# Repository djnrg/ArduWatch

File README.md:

# ArduWatch
Watch Arduino AtHeart

In this project using Arduino Software and following hardweare:
     - ATMega328
     - OLED 1,3" display
     - RTC DS1307
     - Battery 3,7V

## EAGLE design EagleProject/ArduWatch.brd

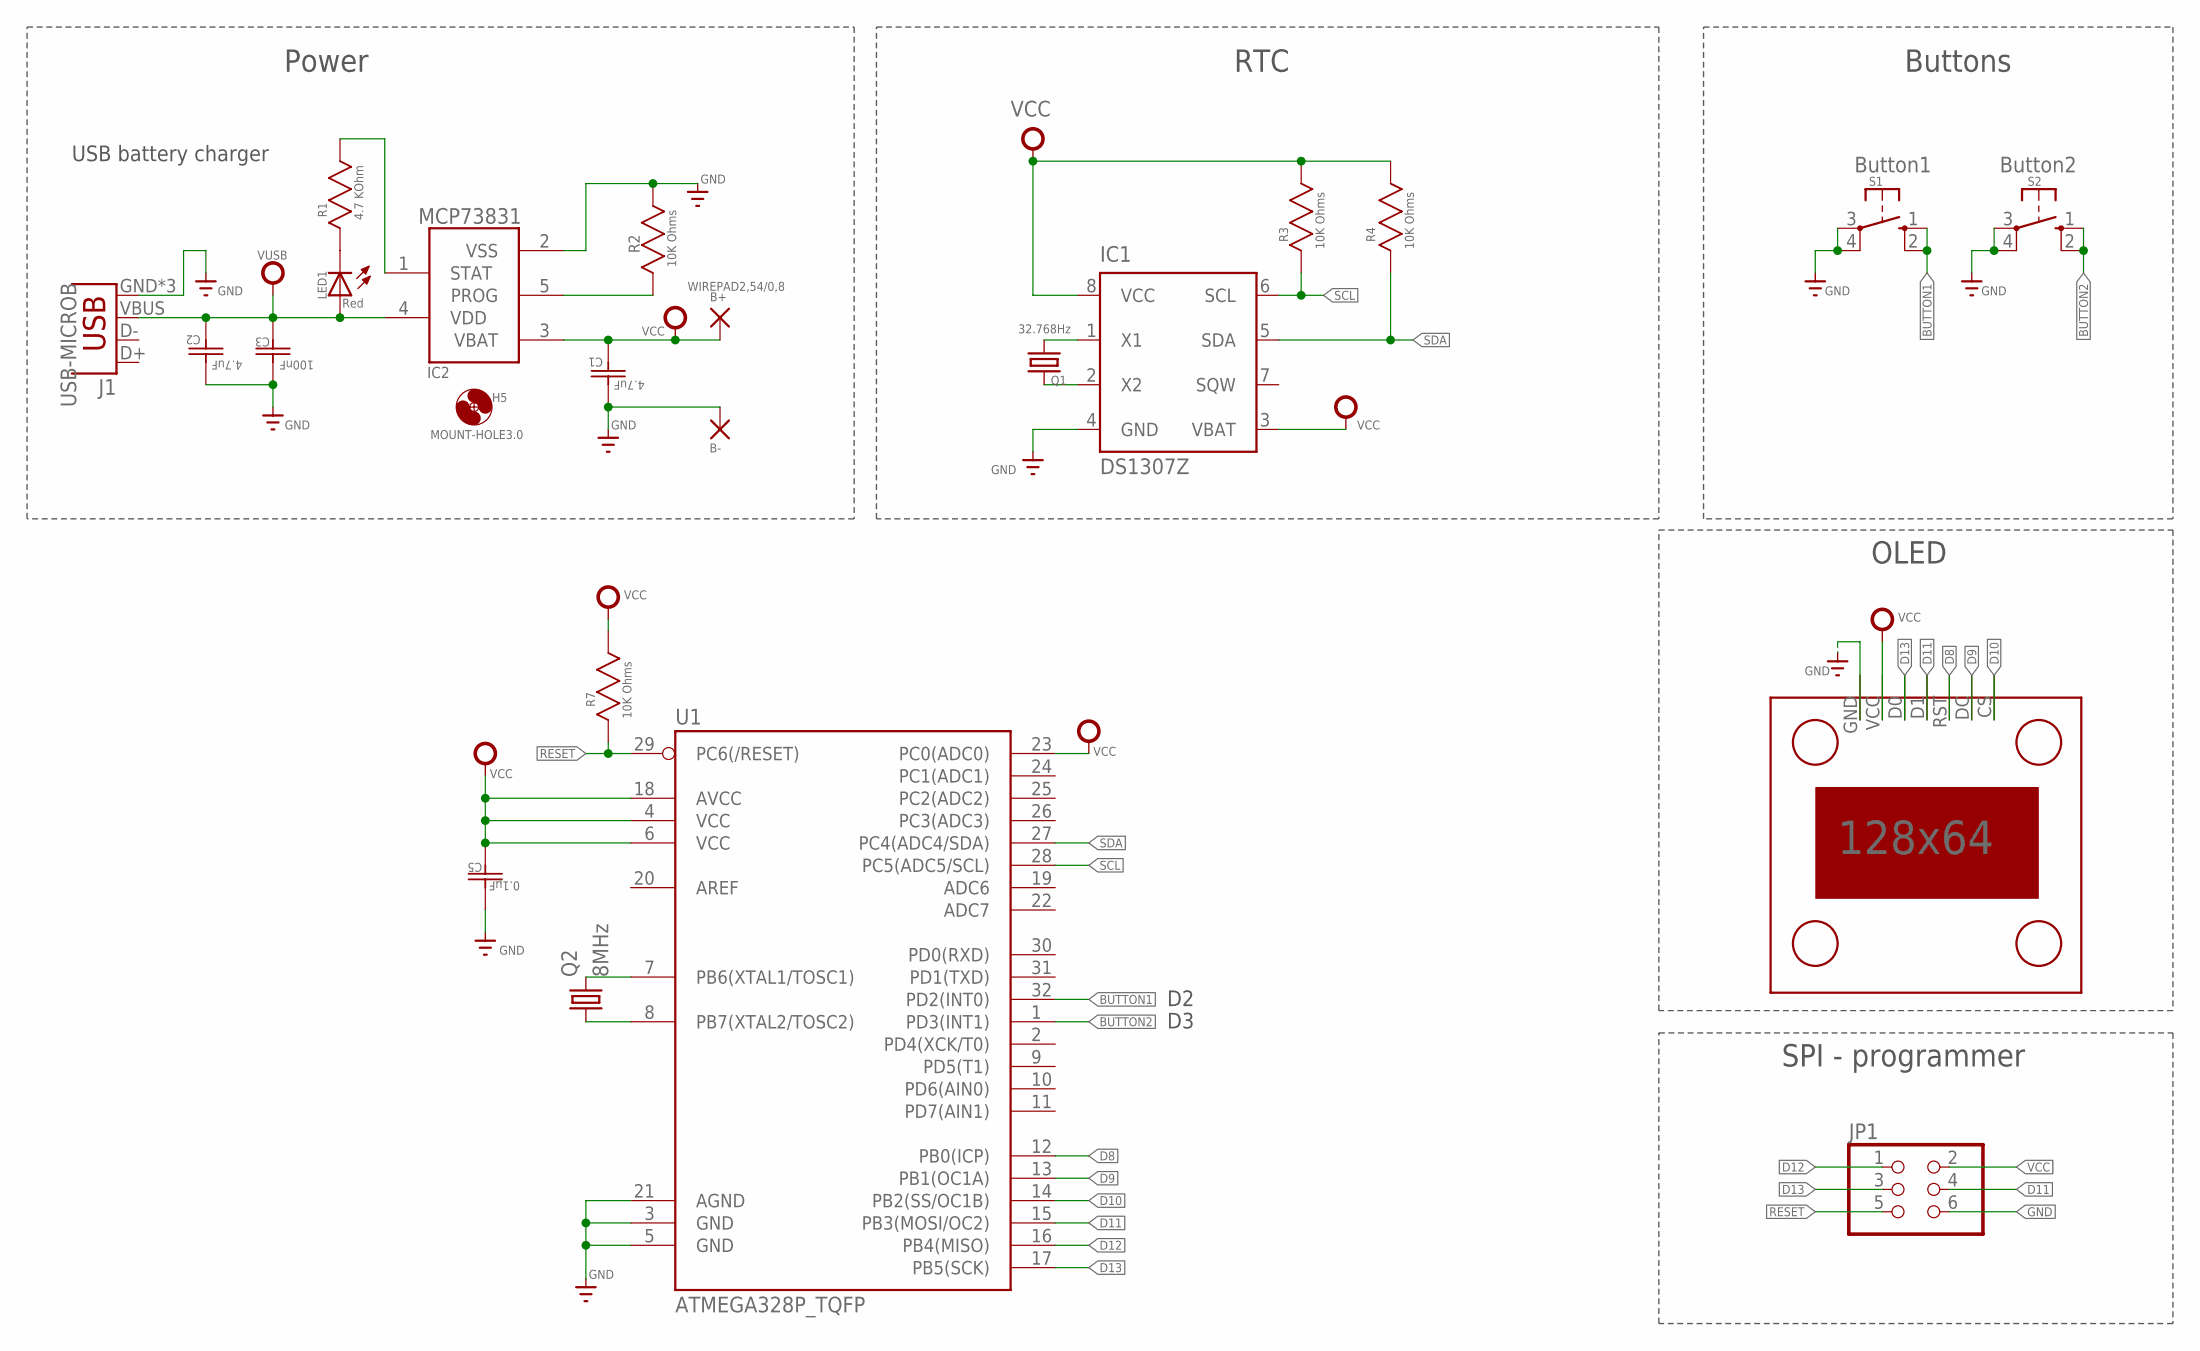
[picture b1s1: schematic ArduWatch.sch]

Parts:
1,3"OLED1: OLED; 1,3"OLED
B+: WIREPAD2,54/0,8; 2,54/0,8
B-: WIREPAD2,54/0,8; 2,54/0,8
C1, C2: 4.7uF; CAPC3216X180N
C3: 100nF; CAPC3216X88N
C5: 0.1µF; CAPC3216X94N
H5: MOUNT-HOLE3.0; 3,0
IC1: DS1307Z; SOIC8
IC2: MCP73831; SOT23-5L
J1: USB-MICROB
JP1: PINHD-2X3; 2X03
LED1: Red; CHIPLED_1206
Q1: 32.768Hz; TC26H
Q2: 8MHz; HC49/S
R1: 4.7 KOhm; RESC3216X71N
R2, R3, R4, R7: 10K Ohms; RESC3216X71N
S1: Button1; B3F-10XX
S2: Button2; B3F-10XX
U1: ATMEGA328P_TQFP; TQFP32-08

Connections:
BUTTON1: S1.1 (S), S1.2 (S1), U1.32 (PD2(INT0))
BUTTON2: S2.1 (S), S2.2 (S1), U1.1 (PD3(INT1))
D8: 1,3"OLED1.RST, U1.12 (PB0(ICP))
D9: 1,3"OLED1.DC, U1.13 (PB1(OC1A))
D10: 1,3"OLED1.CS, U1.14 (PB2(SS/OC1B))
D11: 1,3"OLED1.D1, JP1.4, U1.15 (PB3(MOSI/OC2))
D12: JP1.1, U1.16 (PB4(MISO))
D13: 1,3"OLED1.D0, JP1.3, U1.17 (PB5(SCK))
GND: 1,3"OLED1.GND, B-.1, C1.1 (C1), C2.1 (C1), C3.1 (C1), C5.1 (C1), IC1.4 (GND), IC2.2 (VSS), J1.GND, J1.MT1 (GND), J1.MT2 (GND), JP1.6, R2.1 (R1), S1.3, S1.4 (P1), S2.3, S2.4 (P1), U1.3 (GND), U1.5 (GND), U1.21 (AGND)
unnamed: LED1.C, R1.2 (R2)
unnamed: IC1.1 (X1), Q1.2
unnamed: IC2.1 (STAT), R1.1 (R1)
unnamed: IC2.5 (PROG), R2.2 (R2)
unnamed: IC1.2 (X2), Q1.1
unnamed: Q2.2, U1.7 (PB6(XTAL1/TOSC1))
unnamed: Q2.1, U1.8 (PB7(XTAL2/TOSC2))
RESET: JP1.5, R7.2 (R2), U1.29 (PC6(/RESET))
SCL: IC1.6 (SCL), R3.2 (R2), U1.28 (PC5(ADC5/SCL))
SDA: IC1.5 (SDA), R4.2 (R2), U1.27 (PC4(ADC4/SDA))
VCC: 1,3"OLED1.VCC, B+.1, C1.2 (C2), C5.2 (C2), IC1.3 (VBAT), IC1.8 (VCC), IC2.3 (VBAT), JP1.2, R3.1 (R1), R4.1 (R1), R7.1 (R1), U1.4 (VCC), U1.6 (VCC), U1.18 (AVCC), U1.23 (PC0(ADC0))
VUSB: C2.2 (C2), C3.2 (C2), IC2.4 (VDD), J1.VBUS, LED1.A

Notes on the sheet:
USB battery charger
Power
RTC
Buttons
OLED
SPI - programmer

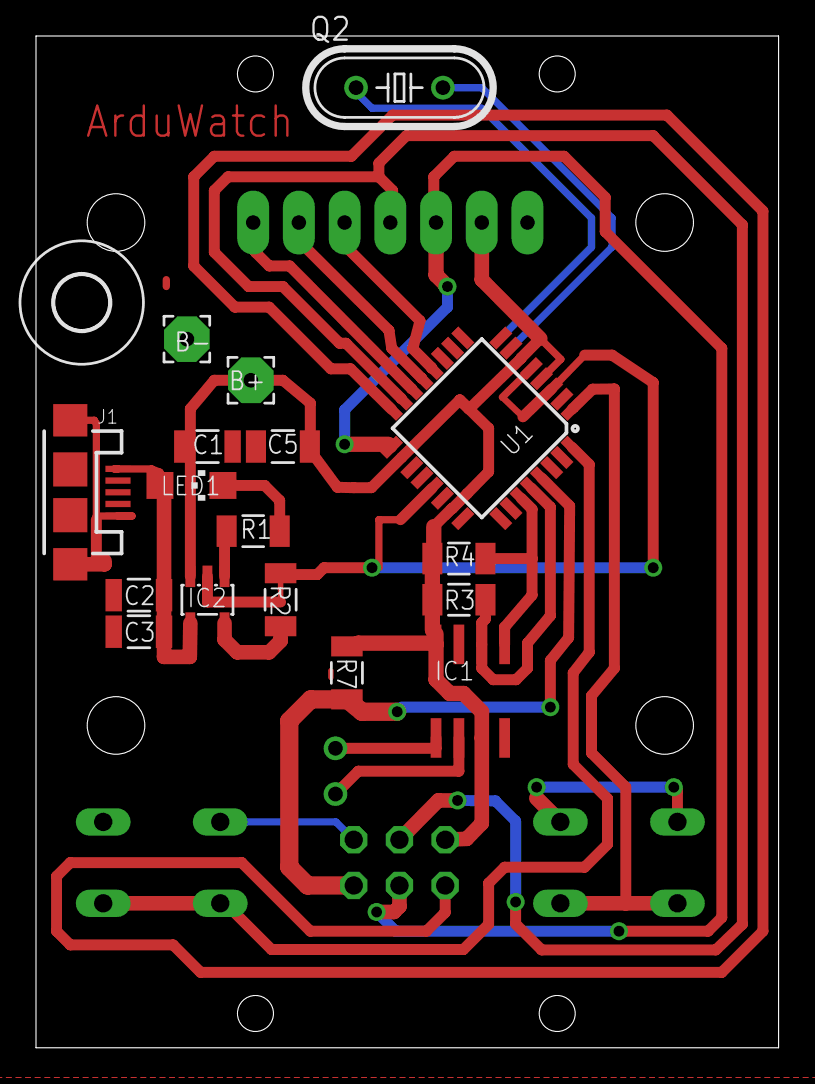
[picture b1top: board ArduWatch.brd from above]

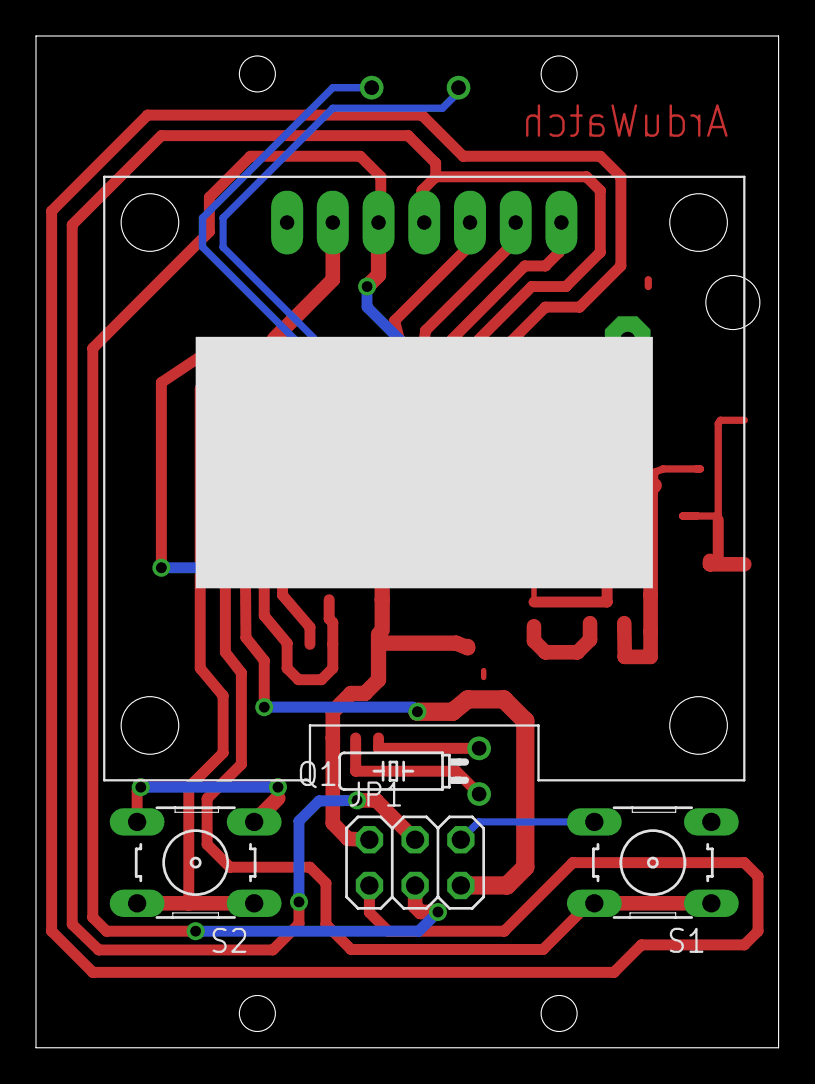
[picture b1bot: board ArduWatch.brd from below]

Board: 2 copper layers, 41.3 x 56.2 mm, 24 parts (5 on the bottom side), 21 nets.

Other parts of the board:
DRILEGEND: DRILEGEND

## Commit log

2016-01-07 Dokumentation
    Add documentation using in progect
2016-01-07 Starting Eage Project
    Start creaing Schematic in Eagle
2016-01-07 Starting Schematic
    Starting Schematic in Eagle
2016-01-09 Schematic V0.2.0
    Schematic version 0.2.0
2016-01-09 Board V0.1.0
    Update board to version 0.1.0
2016-01-09 Schematic PDF
    Release schematic in PDF
2016-01-09 Board V0.2.0
    Update board to version 0.2.0
2016-01-10 PCB release
    PCB release
2016-01-11 PCB - SPI as Arduino
    Change connector for SPI Target
2016-01-13 USB port for charging
    Implement USB port for chrging
2016-02-23 Add CRYSTAL
    Add CRYSTAL 8MHz
2016-02-23 Add Arduino Code
    Temporary code using only microcontrollel without RTC.

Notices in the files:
parts and their libraries:
SparkFun-DigitalIC: Licensing: Creative Commons ShareAlike 4.0 International - https://creativecommons.org/licenses/by-sa/4.0
